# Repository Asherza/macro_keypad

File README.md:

# macro_keypad
Re-programmable macro key pad

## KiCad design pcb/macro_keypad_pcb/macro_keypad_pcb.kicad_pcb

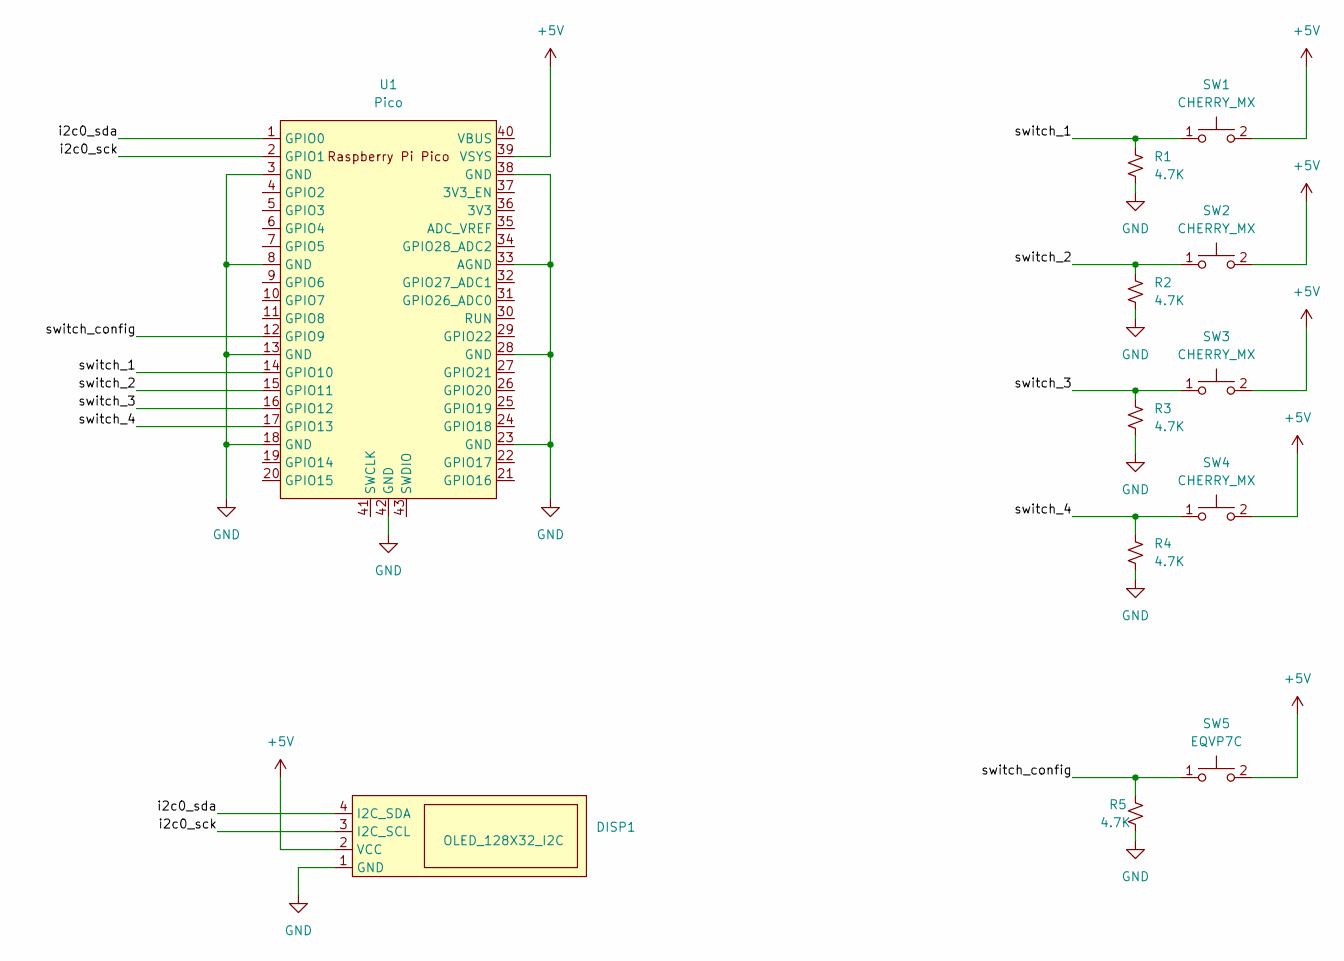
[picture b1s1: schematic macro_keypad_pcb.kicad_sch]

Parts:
DISP1: OLED_128X32_I2C; PinHeader_1x04_P2.54mm_Vertical_SMD_Pin1Left
R1, R2, R3, R4, R5: 4.7K; R_0603_1608Metric
SW1, SW2, SW3, SW4: CHERRY_MX; SW_Cherry_MX_PCB
SW5: EQVP7C; SW_SPST_EVQP7C
U1: Pico; RPi_Pico_SMD_TH

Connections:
+5V: DISP1.2 (VCC), SW1.2, SW2.2, SW3.2, SW4.2, SW5.2, U1.39 (VSYS)
/i2c0_sck: DISP1.3 (I2C_SCL), U1.2 (GPIO1)
/i2c0_sda: DISP1.4 (I2C_SDA), U1.1 (GPIO0)
/switch_1: R1.1, SW1.1, U1.14 (GPIO10)
/switch_2: R2.1, SW2.1, U1.15 (GPIO11)
/switch_3: R3.1, SW3.1, U1.16 (GPIO12)
/switch_4: R4.1, SW4.1, U1.17 (GPIO13)
/switch_config: R5.1, SW5.1, U1.12 (GPIO9)
GND: DISP1.1 (GND), R1.2, R2.2, R3.2, R4.2, R5.2, U1.3 (GND), U1.8 (GND), U1.13 (GND), U1.18 (GND), U1.23 (GND), U1.28 (GND), U1.33 (AGND), U1.38 (GND), U1.42 (GND)

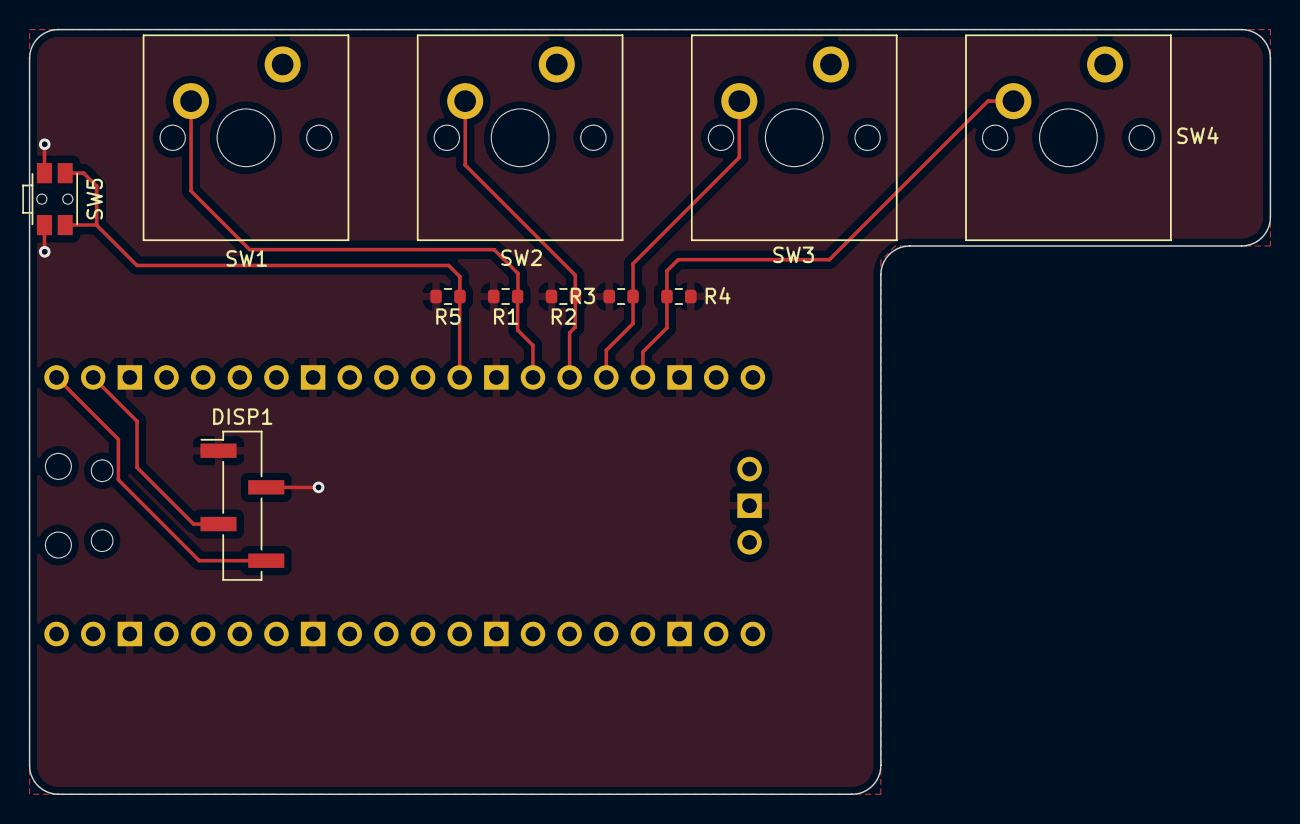
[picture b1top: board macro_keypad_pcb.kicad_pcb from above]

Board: 2 copper layers, 86.0 x 53.0 mm, 12 parts (1 on the bottom side), 9 nets.

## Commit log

2022-02-28 Added case CAD models. Note, FCStd file was created with FreeCAD Linkstage 3
2022-03-04 Added m3 threads and screw holes as an option for printing
2022-03-05 Initial firmware commit
    Added code.py, display_controller, and hid_controller as a base for git
2022-03-08 Added key manager
    Not operational. Added cfg file parsing and assigning to switches based on json contents.
2022-03-09 Added ability to map pins to keys. Also added the ability to see the state of a switch_key
2022-03-12 Updated multiple files, keypad is functional!
    * Broke out key_switch into its own file.
    * Created macro_executor.py to handle parsing macros and executing them.
    * Added ability for key_manager to pass functions to key_switch and manage them.
    * Updated key_switch to be able to add and execute functions, as well as set and get variables.
2022-03-16 Updated Screw cad model to improve insert base not pulling out
    Updated screw cad model to better deal with the screw forces. Also updated directory layout.
2022-04-01 General updates to help with display dev
    prepping for some display development.
    Added a new bmp
    Added removal of keyswitch variables.
    Added some error checking
2022-06-16 first commit of schematic and some various part footprints
2022-06-17 add example PCB layout
2022-07-11 Included DUCYK commands
    Updated to get partial working DUCKY commands running
